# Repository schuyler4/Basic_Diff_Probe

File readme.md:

<h1> 
Basic Diff Probe 
</h1>
I need a differential probe, but I don't need particularly good specs. I don't need very high bandwidth or voltage. This is my solution. 

There are two revisions. The second revision is the same circuit board and circuit as the first revision. The only difference is a compensation
capacitor added in the feedback loop of the split supply buffer to get rid of some oscillation I was seeing.

<h3> Specs </h3>
<ul>
<li> Power Supply: 9V Battery </li>
<li> Bandwidth: 20kHz (1x) / 200Hz (10x) </li>
<li> Offset < 2mV </li>
<li> Maximum Differential Input 10x (1x): 50V (5V) </li>
<li> Minimum Differential Input 10x (1x): -50V (-5V) </li>
<li> Maximum Single Ended Input 10x (1x): 25V (2.5V) </li>
<li> Minimum Differential Input 10x (1x): -25V (-2.5V) </li>
<li> Attenuation Options: 
<ul>
    <li> 10X </li>
    <li> 1X </li>
</ul>
</li>
</ul>
<h3> Example </h3>
Here is an example measurement taken of a sweep from my curve tracer. The purple trace is from the diff probe and the yellow trace is regular single ended oscilloscope measurement.    

<h3> Possible Improvements </h3>
<ol>
<li> For some reason the bandwidth in 10x mode is very low. I'm not sure why this is. </li> 
<li> It is very hard to tell which mode the probe is in (10x or 1x) without looking at a known signal. </li>
</ol>
</p>

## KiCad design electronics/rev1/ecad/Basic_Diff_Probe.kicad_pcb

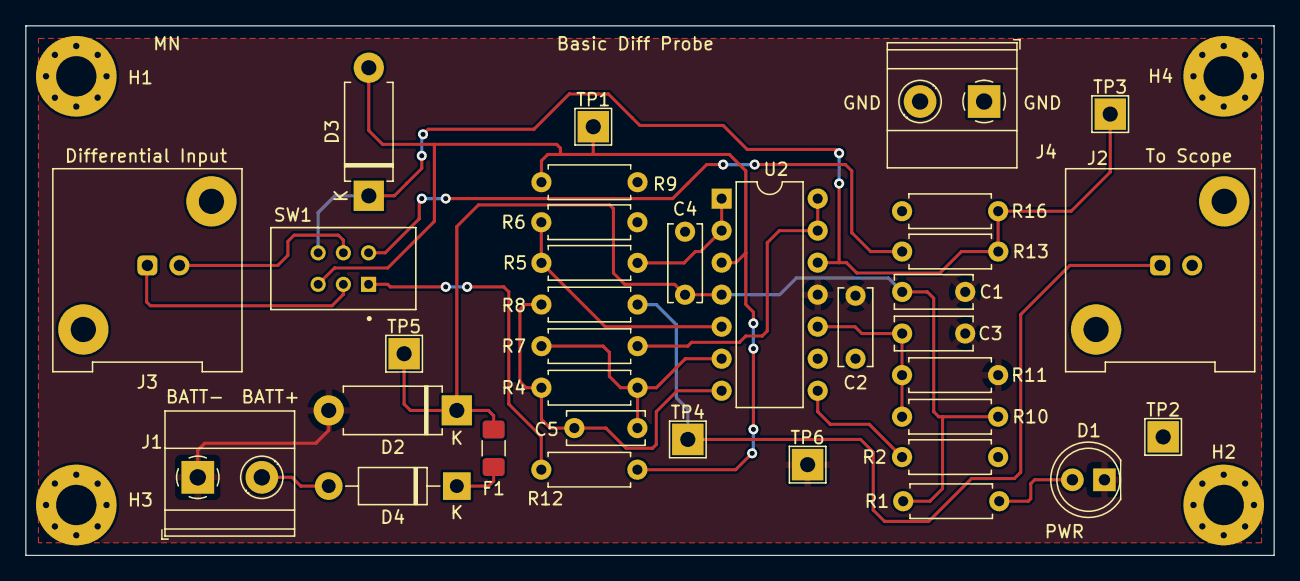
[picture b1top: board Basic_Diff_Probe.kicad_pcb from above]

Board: 2 copper layers, 99.0 x 42.0 mm, 39 parts (0 on the bottom side), 20 nets.

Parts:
C1: 10uF; C_Disc_D6.0mm_W2.5mm_P5.00mm
C2, C3, C4: 0.1uF; C_Disc_D6.0mm_W2.5mm_P5.00mm
C5: 10pF; C_Disc_D6.0mm_W2.5mm_P5.00mm
D1: WP7113ID; LED_D5.0mm
D2: SA10A; D_DO-15_P10.16mm_Horizontal
D3: SA9.0CA; D_DO-15_P10.16mm_Horizontal
D4: 1N5817; D_DO-41_SOD81_P10.16mm_Horizontal
F1: 100mA; Fuse_1206_3216Metric_Pad1.42x1.75mm_HandSolder
H1, H2, H3, H4: M3; MountingHole_3.2mm_M3_Pad_Via
J1: 9V Battery Input; TerminalBlock_Phoenix_MKDS-1,5-2-5.08_1x02_P5.08mm_Horizont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
J2: To Scope; BNC_Amphenol_031-5539_Vertical
J3: Differential Input; BNC_Amphenol_031-5539_Vertical
J4: GND Output; TerminalBlock_Phoenix_MKDS-1,5-2-5.08_1x02_P5.08mm_Horizont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
R1: 1.4k; R_Axial_DIN0207_L6.3mm_D2.5mm_P7.62mm_Horizontal
R2: 0; R_Axial_DIN0207_L6.3mm_D2.5mm_P7.62mm_Horizontal
R4, R5, R6, R7: 10k+/-0.1%; R_Axial_DIN0207_L6.3mm_D2.5mm_P7.62mm_Horizontal
R8: 100; R_Axial_DIN0207_L6.3mm_D2.5mm_P7.62mm_Horizontal
R9, R16: 100k+/-0.1%; R_Axial_DIN0207_L6.3mm_D2.5mm_P7.62mm_Horizontal
R10, R11: 10k; R_Axial_DIN0207_L6.3mm_D2.5mm_P7.62mm_Horizontal
R12, R13: 900k+/-0.1%; R_Axial_DIN0207_L6.3mm_D2.5mm_P7.62mm_Horizontal
SW1: EG2209A; SW_EG2209A
TP1, TP2, TP3, TP4, TP5, TP6: TestPoint; TestPoint_THTPad_2.5x2.5mm_Drill1.2mm
U2: LMC6484AIN; DIP-14_W7.62mm

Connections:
+BATT: C1.1, C4.2, D2.1 (K), F1.2, R1.1, R10.1, TP5.1, U2.4 (V+)
-BATT: C1.2, C2.2, C3.2, D1.1 (K), D2.2 (A), J1.1, R11.2, TP6.1, U2.11 (V-)
GND: C2.1, C4.1, H1.1, H2.1, H3.1, H4.1, J2.2 (Ext), J4.1, J4.2, R2.2, R6.2, R9.2, R16.1, TP2.1, U2.9 (-)
unnamed: C5.2, R4.2, R8.1, U2.7
unnamed: D1.2 (A), R1.2
unnamed: D3.1 (A1), R13.1, R16.2, SW1.6 (C), TP3.1, U2.12 (+)
unnamed: D3.2 (A2), R9.1, R12.2, SW1.3 (C), TP1.1, U2.3 (+)
unnamed: D4.2 (A), J1.2
unnamed: D4.1 (K), F1.1
unnamed: J2.1 (In), R8.2, TP4.1
unnamed: J3.2 (Ext), SW1.5 (B)
unnamed: J3.1 (In), SW1.2 (B)
unnamed: R2.1, U2.8
unnamed: R12.1, SW1.1 (A)
unnamed: R13.2, SW1.4 (A)
unnamed: R5.1, U2.1, U2.2 (-)
unnamed: R5.2, R6.1, U2.5 (+)
unnamed: C5.1, R4.1, R7.2, U2.6 (-)
unnamed: C3.1, R10.2, R11.1, U2.10 (+)
unnamed: R7.1, U2.13 (-), U2.14

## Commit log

2023-09-05 Start of schematic
2023-09-08 schematic
2023-09-22 outputs
2023-09-26 ordered
2023-10-11 chage 0 to 680
2023-10-12 test stuff
2023-10-13 readme
2023-10-13 image
2023-10-13 image file extension
2023-10-13 finished test writeup
2023-10-13 fix types
2023-10-13 fixed typo
2023-12-27 rev2
2023-12-27 fix typo
